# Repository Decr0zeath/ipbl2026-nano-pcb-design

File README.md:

# Nano Quadruped Robot PCB Design - iPBL 2026

A KiCad-based PCB design for servo motor control in a quadruped robot developed for the **International Project Based Learning (iPBL) 2026** program.

| Front | Side |
|-------|------|
|  |  |

## Overview

This project implements a control board for mapping and managing connections to 12 servo motors used in a quadruped robot platform. The board provides power regulation and signal distribution for synchronized leg movement across four legs (3 servos per leg).

## Key Features

- **12 Servo Motor Connections** - Full support for all leg servos (M1-M12)
- **Power Supply Filtering** - Electrolytic capacitors for stable servo power
- **Screw Terminal Connector** - Easy connection to power input
- **Arduino-Compatible** - Compatible with Arduino Nano microcontroller platform
- **Raspberry Pi RX/TX Header** - Mounting holes for serial connection to a Raspberry Pi 4B
- **Compact Design** - Optimized PCB layout for integration into robot chassis

## Component Reference

| Reference | Component | Quantity | Purpose |
|-----------|-----------|----------|---------|
| A1 | Arduino Nano | 1 | Main microcontroller |
| M1-M12 | SG90 servo motor connections | 12 | Motor control for quadruped legs |
| C1, C2 | 470uF Electrolytic Capacitor | 2 | Power supply filtering |
| C3 | 100uF Electrolytic Capacitor | 1 | Power supply filtering |
| J3 | Straight 5mm Plugin Screw Terminal DB301V-5.0-2P | 1 | Power input connector |
| R1 | 330 ohm 1/4 watt Resistor | 1 | Current limiting for LED |
| D1 | LED | 1 | Power/status indicator |
| H1, H2 | Mounting holes | 2 | Jumper wire power switch |
| H3, H4 | Mounting holes | 2 | RX/TX connection from Nano to another microcontroller (Raspberry Pi 4B) |

## Servo Motor Configuration

The 12 servos are organized by quadruped legs:
- **Front Left Leg**: M1, M2, M3
- **Front Right Leg**: M4, M5, M6
- **Rear Left Leg**: M7, M8, M9
- **Rear Right Leg**: M10, M11, M12

## Board Views

Shown in color (rather than plain black) so they stay readable against GitHub's dark theme.

| Front Silkscreen | Bottom Copper Layer |
|------------------|---------------------|
|  |  |

### Schematic

## Design Specifications

- **PCB Layers**: 2-layer design
- **Pad Drill Size**: Standard 0.4mm
- **Track Width**: 0.25mm (default)
- **Via Diameter**: 0.6mm / 0.4mm drill
- **Design Rules**: Checked for clearance and connectivity

## Files

- `nano_IPBL_2026.kicad_sch` - Schematic design
- `nano_IPBL_2026.kicad_pcb` - PCB layout
- `nano_IPBL_2026.kicad_pro` - KiCad project file
- `nano_IPBL_2026.kicad_prl` - Project runtime library
- `exports/nano_IPBL_2026_schematic.svg` - Full schematic view
- `exports/nano_IPBL_2026-F_Silkscreen_colored.svg` - Front silkscreen view, colored (`*_black.svg` for plain black)
- `exports/nano_IPBL_2026-B_Cu_colored.svg` - Bottom copper layer, colored (`*_black.svg` for plain black)
- `exports/3dview_front.png` / `exports/3dview_side.png` - Expected 3D renders of the board

## Getting Started

### Prerequisites
- KiCad 10.0+ (used for design and editing)
- Compatible microcontroller (Arduino Nano recommended)
- Servo motors with standard 3-wire connectors
- Power supply (typical: 5-6V for servo operation)

### Opening the Project
1. Open KiCad
2. File → Open → Select `nano_IPBL_2026.kicad_pro`
3. Double-click to view the schematic or layout

### Fabrication
- Generate Gerber files from `nano_IPBL_2026.kicad_pcb` for PCB manufacturing
- Use the included design rules for manufacturing tolerances
- Standard 2-layer PCB process compatible

## Power Budget

- **Power Source**: 2x 3.7V AA batteries in series (7.4V total)
- **Voltage Regulation**: External XL4015E1 buck converter steps down 7.4V to 5V (not part of the PCB)
- **Servo Motor Draw**: ~100-500mA per servo (depending on load)
- **Total Potential Draw**: Up to 6A for all 12 servos

## Notes

- Lock files (.lck) are not included in version control (ignored by .gitignore)
- SVG layer exports provide visual reference of copper traces
- Design includes DRC (Design Rule Check) exclusions for known non-critical issues
- All servo connections use standard 3-wire Futaba/HiTec/JR connectors

## Credits

This design is based on the original [Quadruped Spider Robot (3D Printed Parts, SG90 Servo Motor, Arduino Nano)](https://www.pcbway.com/project/shareproject/Quadruped_Spider_Robot_3D_Printed_Parts_SG90_Servo_Motor_Arduino_Nano_10107fe3.html) project shared on PCBWay. This repository branches off that design with improvements including revised switch/regulator ordering, larger vias and copper pads, and a rearranged component layout.

## License

Part of iPBL 2026 International Project Based Learning Program

---

*Last updated: 2026-07-21*

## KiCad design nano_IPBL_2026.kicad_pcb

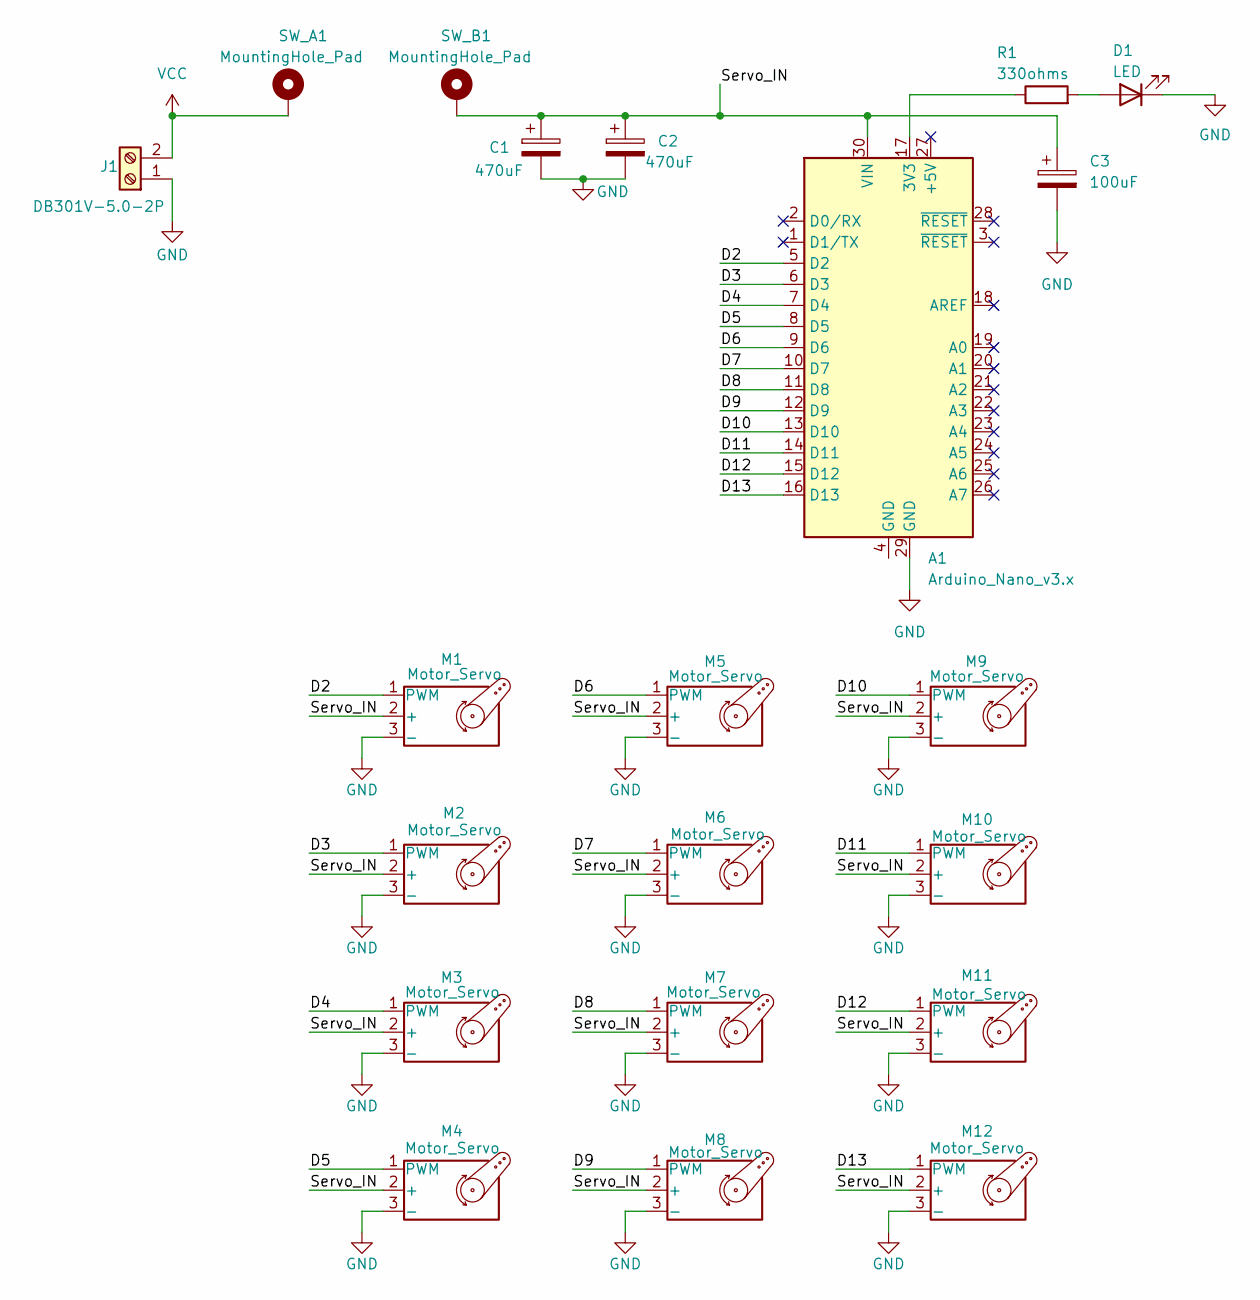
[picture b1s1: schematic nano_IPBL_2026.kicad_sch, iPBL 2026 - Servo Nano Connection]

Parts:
A1: Arduino_Nano_v3.x; Arduino_Nano
C1, C2: 470uF; CP_Radial_D6.3mm_P2.50mm
C3: 100uF; CP_Radial_D6.3mm_P2.50mm
D1: LED; LED_D5.0mm
J1: DB301V-5.0-2P; CONN-TH_2P-P5.00_L7.6-W10.0; LCSC Part C395882
M1, M2, M3, M4, M5, M6, M7, M8, M9, M10, M11, M12: Motor_Servo; PinHeader_1x03_P2.54mm_Vertical
R1: 330ohms; R_Axial_DIN0207_L6.3mm_D2.5mm_P2.54mm_Vertical
SW_A1: MountingHole_Pad; MountingHole_1.2mm_M2_Pad_EDITED
SW_B1: MountingHole_Pad; MountingHole_1.2mm_M2_Pad_EDITED

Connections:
/D2: A1.5 (D2), M1.1 (PWM)
/D3: A1.6 (D3), M2.1 (PWM)
/D4: A1.7 (D4), M3.1 (PWM)
/D5: A1.8 (D5), M4.1 (PWM)
/D6: A1.9 (D6), M5.1 (PWM)
/D7: A1.10 (D7), M6.1 (PWM)
/D8: A1.11 (D8), M7.1 (PWM)
/D9: A1.12 (D9), M8.1 (PWM)
/D10: A1.13 (D10), M9.1 (PWM)
/D11: A1.14 (D11), M10.1 (PWM)
/D12: A1.15 (D12), M11.1 (PWM)
/D13: A1.16 (D13), M12.1 (PWM)
/Servo_IN: A1.30 (VIN), C1.1, C2.1, C3.1, M1.2 (+), M2.2 (+), M3.2 (+), M4.2 (+), M5.2 (+), M6.2 (+), M7.2 (+), M8.2 (+), M9.2 (+), M10.2 (+), M11.2 (+), M12.2 (+), SW_B1.1; also elsewhere on the board
GND: A1.29 (GND), C1.2, C2.2, C3.2, D1.1 (K), J1.1, M1.3 (-), M2.3 (-), M3.3 (-), M4.3 (-), M5.3 (-), M6.3 (-), M7.3 (-), M8.3 (-), M9.3 (-), M10.3 (-), M11.3 (-), M12.3 (-)
unnamed: A1.17 (3V3), R1.1
unnamed: D1.2 (A), R1.2
VCC: J1.2, SW_A1.1 (Pin_1_1)

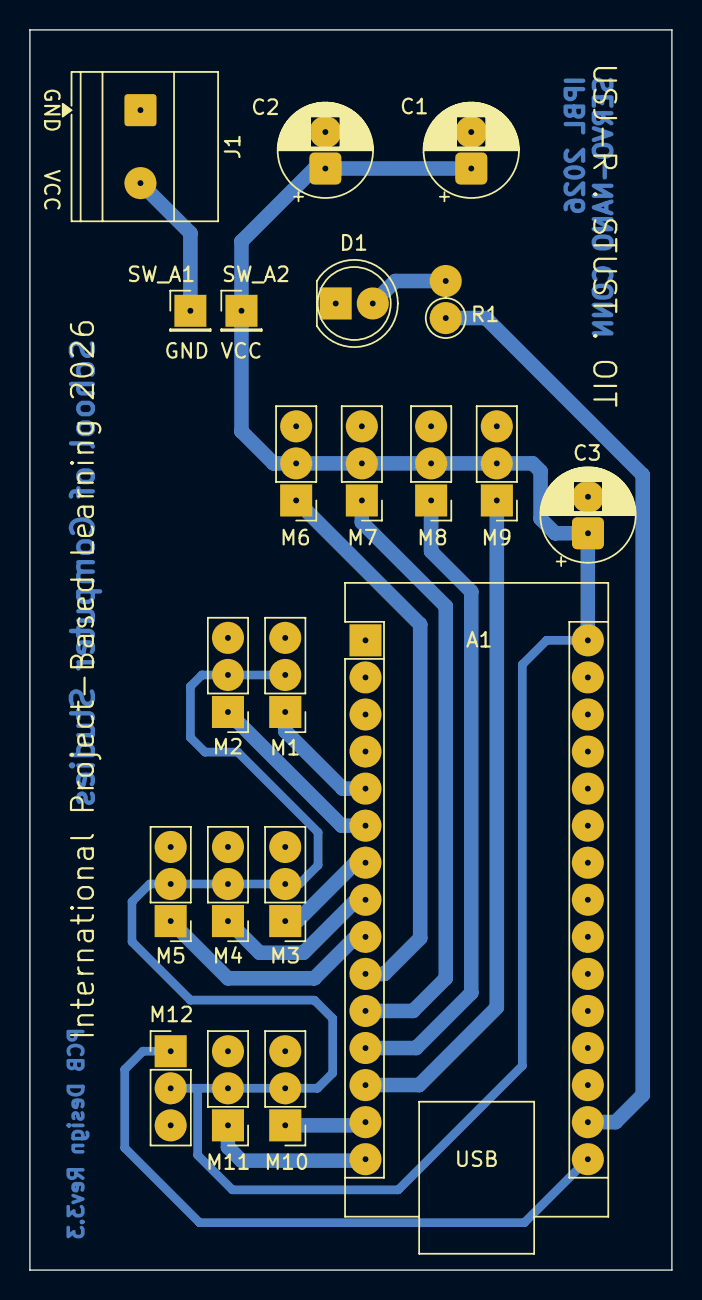
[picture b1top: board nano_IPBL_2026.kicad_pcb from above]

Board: 2 copper layers, 44.0 x 85.0 mm, 21 parts (0 on the bottom side), 17 nets.

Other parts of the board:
SW_A2: Conn_01x01_Pin; PinHeader_1x01_P2.54mm_Vertical

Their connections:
/Servo_IN: SW_A2.1 (Pin_1_1); also elsewhere on the board
